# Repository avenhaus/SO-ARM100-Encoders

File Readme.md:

# <center>Magnetic Encoder Dummy Servo</center>

## Summary
This project is related to 
https://github.com/huggingface/lerobot
and
https://github.com/TheRobotStudio/SO-ARM100

It explores to use much cheaper magnetic encoders for the Leader Arm instead of the regular servos. These dummy servos are also much easier to move manually, as there is no gear train that needs to back drive the servo motor. This makes them ideal for the Leader Arm.

## Custom PCB

The custom PCB makes it possible to daisy chain magnetic encoders for much easier wiring. The PCB uses a microcontroller that emulates a FeeTech servo. The dummy servos can be connected to the same servo controller board and no special software is needed.

### Manufacturing
TODO: JLCPCB

### Cables and Connectors

FeeTech servos use 3-pin 5264 connectors. However, JST XH connectors are more common and pre-made cables are much easier to find. The PCB can be populated with either of the connector types. If JST connectors are used, an adapter needs to be made to connect to the 5264 connector on the controller board. Alternatively one can simply cut off one end from a pre-made cable and solder it directly to the controller board.

The dummy servos use very little current. So any gauge wire should be ok. However, if they are to be mixed with real servos on the same bus, wire gauge needs to be taken into consideration.

The servos use "reverse double head" cables (pin 1 connected to pin 1, etc.) although in a pinch it's also possible to switch the terminals on "same side' cables yourself.

JST XH: https://www.aliexpress.us/w/wholesale-JST-XH-3.html
JST XH cables: https://www.aliexpress.us/w/wholesale-xh-double-head.html

5264: https://www.aliexpress.us/w/wholesale-5264.html
5264 cables: https://www.aliexpress.us/w/wholesale-5264-double-head.html https://www.aliexpress.us/item/3256806128255434.html

### Magnets

Normally magnetic encoders use special, radially magnetized magnets.

Magnets https://www.aliexpress.us/w/wholesale-encoder-magnets.htm

However, it is also possible to use the regular, axially magnetized 6x3 disk magnets which are cheaper. They just have to be oriented sideways. Print the corresponding servo horn instead. N35 magnets are fine. Nothing fancy is needed.

https://www.amazon.com/s?k=6x3mm+magnet
https://www.aliexpress.us/w/wholesale-6x3-magnet.html

### Firmware Programming

See: [Firmware](Firmware)

### 3D Printed Servo Housing

## Off the Shelve Hardware

Instead of using a custom PCB it is also possible to use off the shelve parts. This requires more hand wiring.

### Magnetic Rotary Encoders
Currently there are two cheap and popular magnetic encoders on AliExpress, the AS5600 and the MT6701.
The AS5600 is older, has 12 bit resolution (4096) and supports only I2C. Since the chip has only one hard coded ID, that makes it hard to use when multiple of them are needed.
The MT6701 has 14 bit resolution (16,383) and also supports a SSI interface, which is similar to SPI.

AliExpress offers several MT6701 breakout boards some of which can be purchased in low quantities for less than $2 including magnet.

[AliExp MT6701](https://www.aliexpress.com/w/wholesale-MT6701.html)

<p>

The larger version only has the I2C pins on the header and must be modified to work with SSI. The trace to the middle pin of the header needs to be cut and IC pin 8 lifted and connected to that header pin instead. It is also slightly too large, sticking out a bit in front of the servo. It can be made to work, but the smaller board is much easier to use and therefor recommended. However the smaller board does not come with magnets. They must be purchased separately. Only radially magnetized magnets can be used. Normally disk magnets are magnetized axially. 

[AliExp Radial Magnets](https://www.aliexpress.us/item/3256804628068823.html)

### 3D Printed Servo Housing

There are two slightly different versions of the housing. The simple version does not retain the servo horns by itself. It relies on the structure of the robot arm to keep them in place. This version is slightly simpler and is used for the lower 4 arm servos.

The wrist and gripper need the horn to be held in place by the servo itself. For these joints the top is split into two parts and the horn axle is not just a straight cylinder.

**Big Board Alternative**

The [Dummy Servo](./Hardware) is 3D printed.

## Software

A simple [Arduino](./Arduino) / PlatformIO project is used to read the six encoders and send their values over a serial USB port to the PC.

On the PC side a small [Python](./Python) program receives the values from the serial port and uses the Feetech-SDK to control the servos of the follower arm.

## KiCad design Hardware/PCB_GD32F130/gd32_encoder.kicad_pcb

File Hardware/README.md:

# <center>3D Models</center>

## Custom PCB

The PCB can be populated with either an AS5600 or an MT6701 encoder. The MCU can automatically figure out which one is connected. However at the moment there are only non blocking drivers for the AS5600.

There are two versions of the PCB. One for the GD32F130 microcontroller, which is also used by Feetech servos. The other one uses a CH32V003 instead, which is cheaper. However no firmware has been written yet for the CH32V003 and the PCB has not been tested.

### Programming Dongles

The GD32F130 is programmed with a ST-LINK V2 dongle: https://www.aliexpress.us/item/3256805941217455.html / https://www.aliexpress.us/item/3256805308308820.html

The CH32V003  is programmed with a WCH-linkE dongle: https://www.aliexpress.us/item/3256804084637506.html

### Solder Stencil

[Cutting solder paste stencils from Mylar YouTube video](https://www.youtube.com/watch?v=mw0mskVCvis)
[make_stencil.py GitHub](https://github.com/bminch/Eclectronics)

- Open KicCAD PCB => Plot 
- Select layers: F. Paste and Edge Cuts
- Plot Format: SVG
- python make_stencil.py gd32_encoder

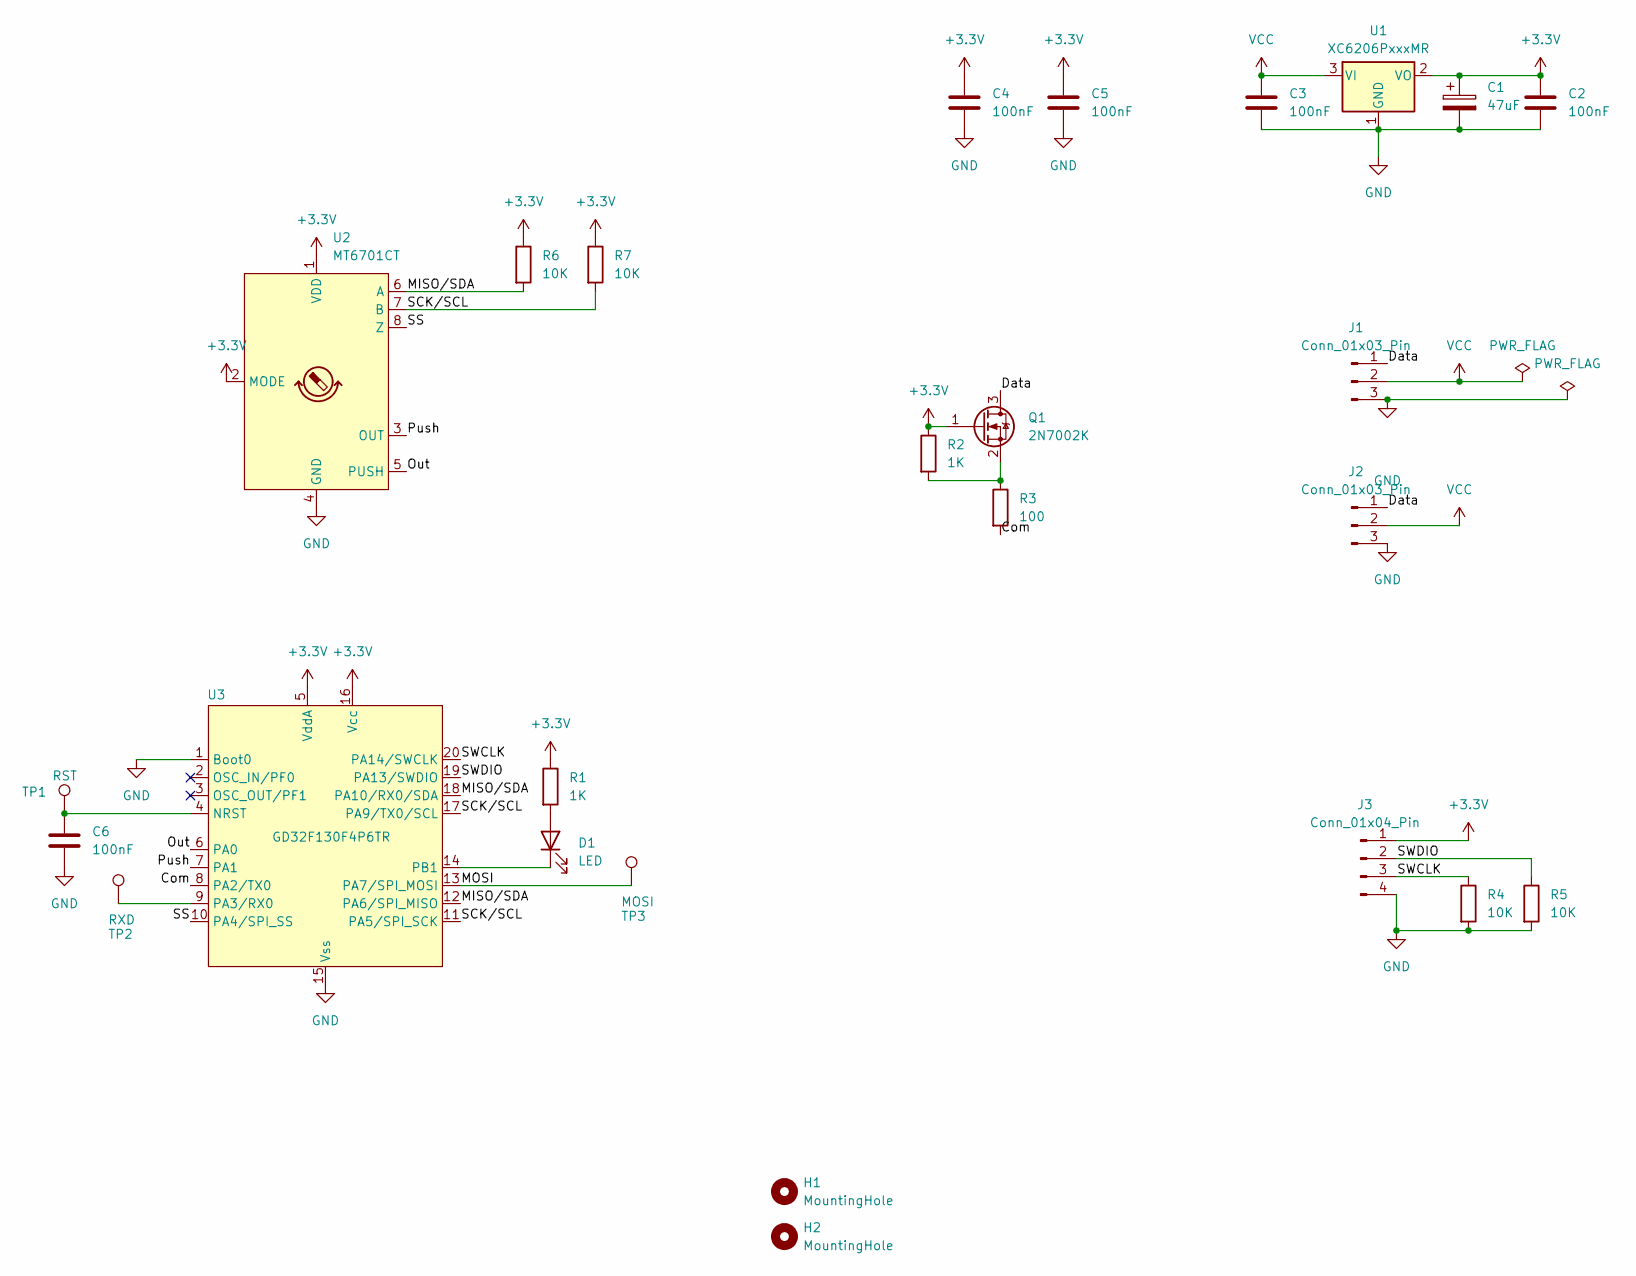
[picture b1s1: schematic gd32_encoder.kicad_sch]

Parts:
C1: 47uF; CP_EIA-3216-18_Kemet-A_Pad1.58x1.35mm_HandSolder
C2, C3, C4, C5, C6: 100nF; C_0603_1608Metric_Pad1.08x0.95mm_HandSolder
D1: LED; LED_0603_1608Metric_Pad1.05x0.95mm_HandSolder
H1, H2: MountingHole; MountingHole_2.2mm_M2_DIN965
J1, J2: Conn_01x03_Pin; JST_1x03_P2.50mm_Vertical
J3: Conn_01x04_Pin; PinHeader_1x04_P2.54mm_Vertical
Q1: 2N7002K; SOT-23
R1, R2: 1K; R_0603_1608Metric_Pad0.98x0.95mm_HandSolder
R3: 100; R_0603_1608Metric_Pad0.98x0.95mm_HandSolder
R4, R5, R6, R7: 10K; R_0603_1608Metric_Pad0.98x0.95mm_HandSolder
TP1: RST; PinHeader_1x01_P2.54mm_Vertical
TP2: RXD; TestPoint_Pad_D1.0mm
TP3: MOSI; TestPoint_Pad_D1.0mm
U1: XC6206PxxxMR; SOT-23-3
U2: MT6701CT; SO-8_3.9x4.9mm_P1.27mm
U3: GD32F130F4P6TR; TSSOP-20_4.4x6.5mm_P0.65mm

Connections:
+3.3V: C1.1, C2.1, C4.1, C5.1, J3.1, Q1.1 (G), R1.1, R2.1, R6.1, R7.1, U1.2 (VO), U2.1 (VDD), U2.2 (MODE), U3.5 (VddA), U3.16 (Vcc)
/Com: R3.2, U3.8 (PA2/TX0)
/Data: J1.1, J2.1, Q1.3 (D)
/MISO/SDA: R6.2, U2.6 (A), U3.12 (PA6/SPI_MISO), U3.18 (PA10/RX0/SDA)
/MOSI: TP3.1, U3.13 (PA7/SPI_MOSI); also elsewhere on the board
/Out: U2.5 (PUSH), U3.6 (PA0)
/Push: U2.3 (OUT), U3.7 (PA1)
/SCK/SCL: R7.2, U2.7 (B), U3.11 (PA5/SPI_SCK), U3.17 (PA9/TX0/SCL)
/SS: U2.8 (Z), U3.10 (PA4/SPI_SS)
/SWCLK: J3.3, R4.1, U3.20 (PA14/SWCLK)
/SWDIO: J3.2, R5.1, U3.19 (PA13/SWDIO)
GND: C1.2, C2.2, C3.2, C4.2, C5.2, C6.2, J1.3, J2.3, J3.4, R4.2, R5.2, U1.1 (GND), U2.4 (GND), U3.1 (Boot0), U3.15 (Vss)
unnamed: D1.2 (A), R1.2
unnamed: D1.1 (K), U3.14 (PB1)
unnamed: Q1.2 (S), R2.2, R3.1
unnamed: C6.1, TP1.1, U3.4 (NRST)
unnamed 16: TP2.1, U3.9 (PA3/RX0); also elsewhere on the board
VCC: C3.1, J1.2, J2.2, U1.3 (VI)

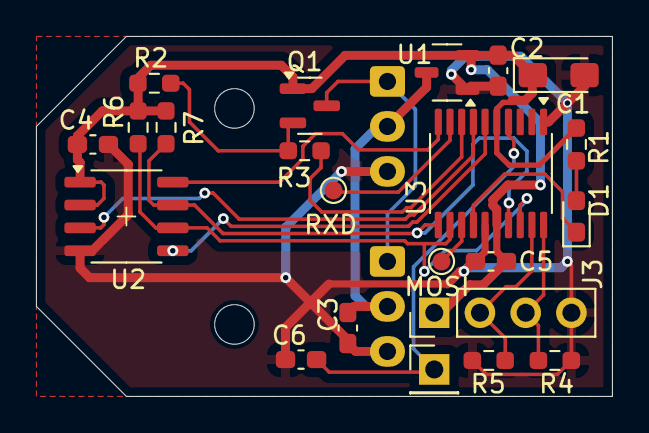
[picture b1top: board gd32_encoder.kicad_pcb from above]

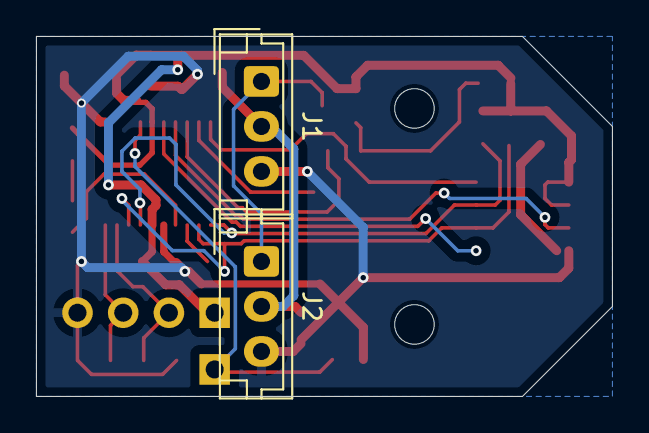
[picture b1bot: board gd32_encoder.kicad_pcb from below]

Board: 2 copper layers, 32.0 x 20.0 mm, 26 parts (2 on the bottom side), 18 nets.

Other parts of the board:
MOSI: MOSI; TestPoint_Pad_D1.0mm
RXD: RXD; TestPoint_Pad_D1.0mm

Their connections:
/MOSI: MOSI.1; also elsewhere on the board
unnamed 16: RXD.1; also elsewhere on the board

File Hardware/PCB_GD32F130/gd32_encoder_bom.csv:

Id,Designator,Footprint,Quantity,Designation,Supplier and ref
1,"R4,R5,R7,R6",R_0603_1608Metric_Pad0.98x0.95mm_HandSolder,4,10K,
4,C1,CP_EIA-3216-18_Kemet-A_Pad1.58x1.35mm_HandSolder,1,47uF,
5,"C2,C5,C3,C6,C4",C_0603_1608Metric_Pad1.08x0.95mm_HandSolder,5,100nF,
6,"R1,R2",R_0603_1608Metric_Pad0.98x0.95mm_HandSolder,2,1K,
7,U3,TSSOP-20_4.4x6.5mm_P0.65mm,1,GD32F130F4P6TR,
8,U2,SO-8_3.9x4.9mm_P1.27mm,1,MT6701CT,
9,R3,R_0603_1608Metric_Pad0.98x0.95mm_HandSolder,1,100,
11,D1,LED_0603_1608Metric_Pad1.05x0.95mm_HandSolder,1,LED,
12,U1,SOT-23-3,1,XC6206PxxxMR,
14,Q1,SOT-23,1,2N7002K,

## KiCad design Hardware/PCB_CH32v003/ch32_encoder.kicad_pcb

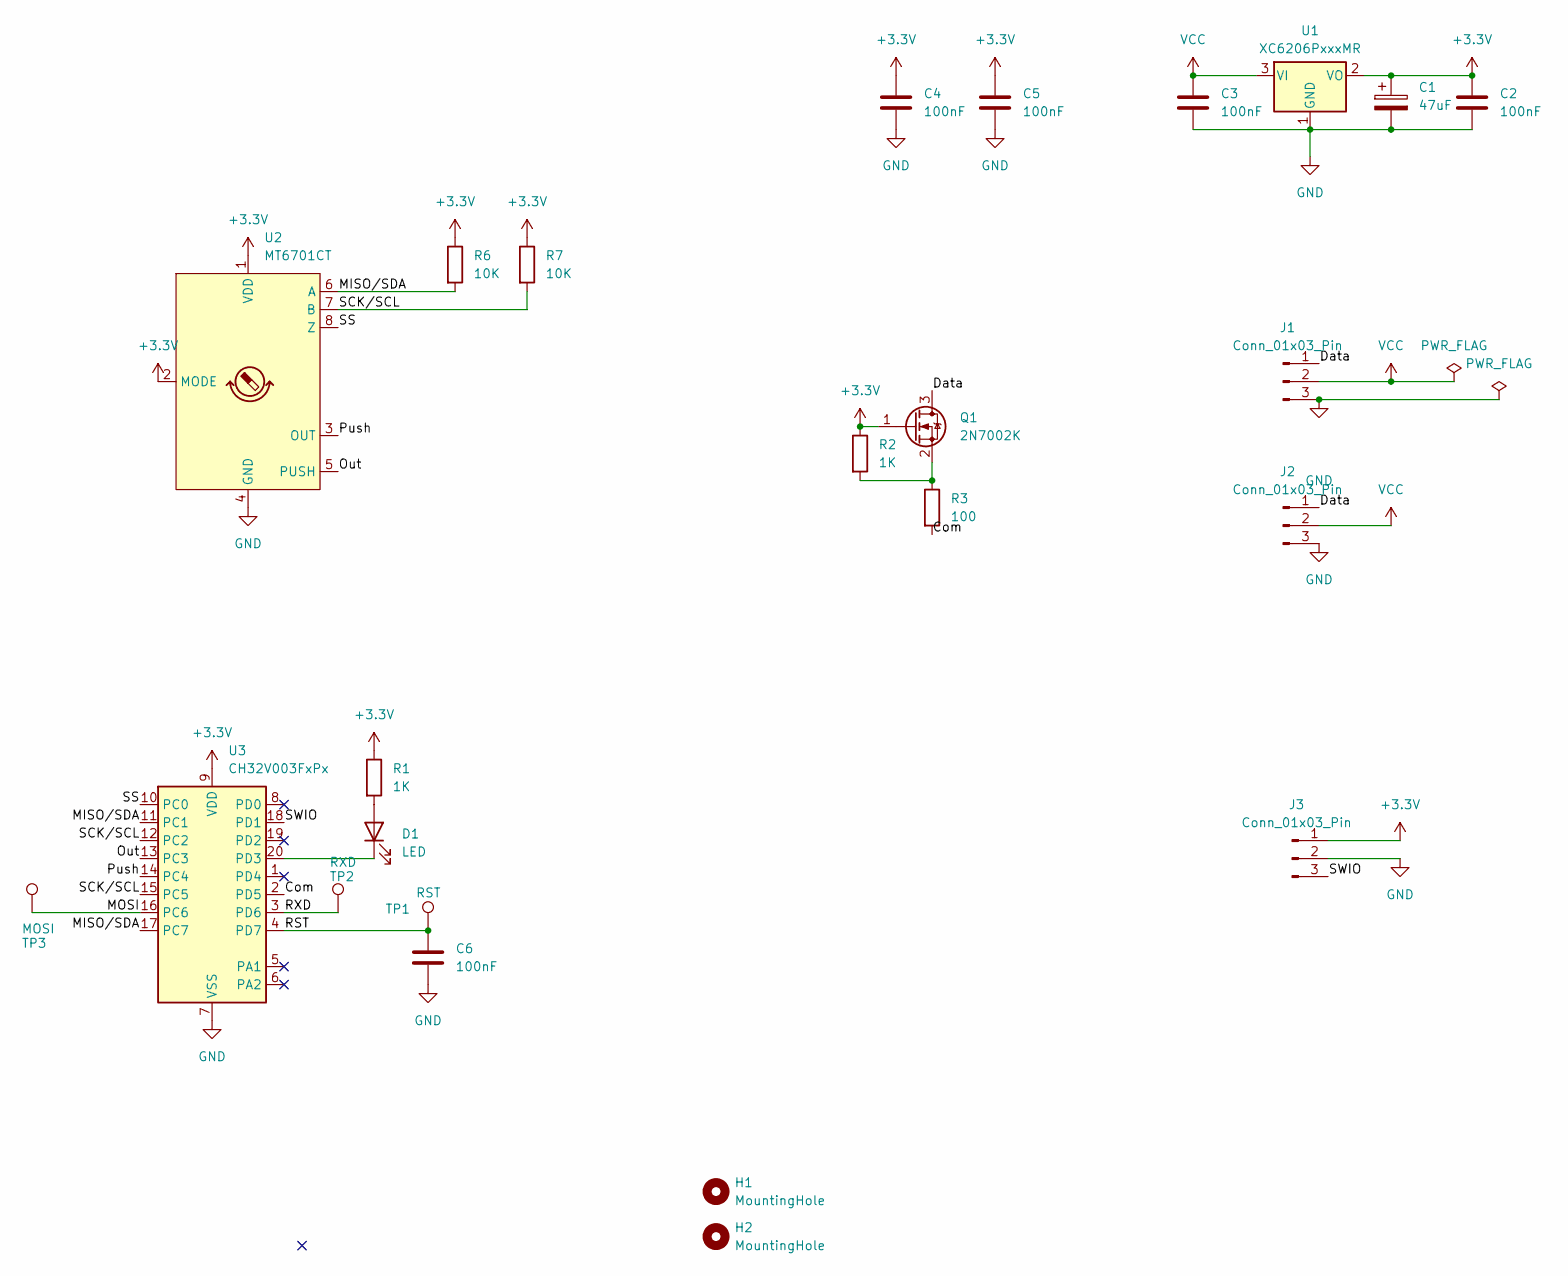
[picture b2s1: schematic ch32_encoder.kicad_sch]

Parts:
C1: 47uF; CP_EIA-3216-18_Kemet-A_Pad1.58x1.35mm_HandSolder
C2, C3, C4, C5, C6: 100nF; C_0603_1608Metric_Pad1.08x0.95mm_HandSolder
D1: LED; LED_0603_1608Metric_Pad1.05x0.95mm_HandSolder
H1, H2: MountingHole; MountingHole_2.2mm_M2_DIN965
J1, J2: Conn_01x03_Pin; JST_1x03_P2.50mm_Vertical
J3: Conn_01x03_Pin; PinHeader_1x03_P2.54mm_Vertical
Q1: 2N7002K; SOT-23
R1, R2: 1K; R_0603_1608Metric_Pad0.98x0.95mm_HandSolder
R3: 100; R_0603_1608Metric_Pad0.98x0.95mm_HandSolder
R6, R7: 10K; R_0603_1608Metric_Pad0.98x0.95mm_HandSolder
TP1: RST; PinHeader_1x01_P2.54mm_Vertical
TP2: RXD; TestPoint_Pad_D1.0mm
TP3: MOSI; TestPoint_Pad_D1.0mm
U1: XC6206PxxxMR; SOT-23-3
U2: MT6701CT; SO-8_3.9x4.9mm_P1.27mm
U3: CH32V003FxPx; TSSOP-20_4.4x6.5mm_P0.65mm

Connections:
+3.3V: C1.1, C2.1, C4.1, C5.1, J3.1, Q1.1 (G), R1.1, R2.1, R6.1, R7.1, U1.2 (VO), U2.1 (VDD), U2.2 (MODE), U3.9 (VDD)
/Com: R3.2, U3.2 (PD5)
/Data: J1.1, J2.1, Q1.3 (D)
/MISO/SDA: R6.2, U2.6 (A), U3.11 (PC1), U3.17 (PC7)
/MOSI: TP3.1, U3.16 (PC6); also elsewhere on the board
/Out: U2.5 (PUSH), U3.13 (PC3)
/Push: U2.3 (OUT), U3.14 (PC4)
/RST: C6.1, TP1.1, U3.4 (PD7)
/RXD: TP2.1, U3.3 (PD6); also elsewhere on the board
/SCK/SCL: R7.2, U2.7 (B), U3.12 (PC2), U3.15 (PC5)
/SS: U2.8 (Z), U3.10 (PC0)
/SWIO: J3.3, U3.18 (PD1)
GND: C1.2, C2.2, C3.2, C4.2, C5.2, C6.2, J1.3, J2.3, J3.2, U1.1 (GND), U2.4 (GND), U3.7 (VSS)
unnamed: D1.2 (A), R1.2
unnamed: D1.1 (K), U3.20 (PD3)
unnamed: Q1.2 (S), R2.2, R3.1
VCC: C3.1, J1.2, J2.2, U1.3 (VI)

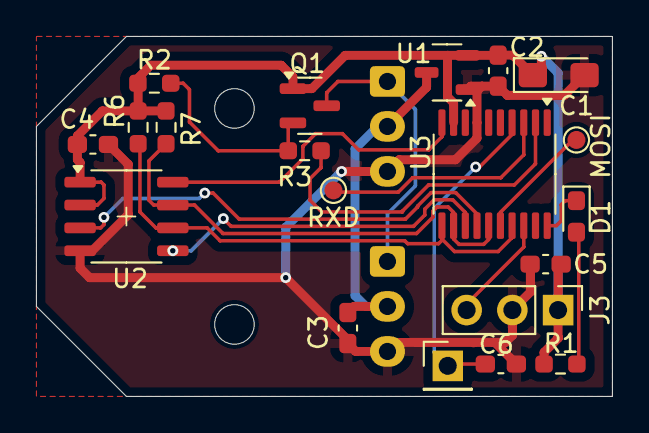
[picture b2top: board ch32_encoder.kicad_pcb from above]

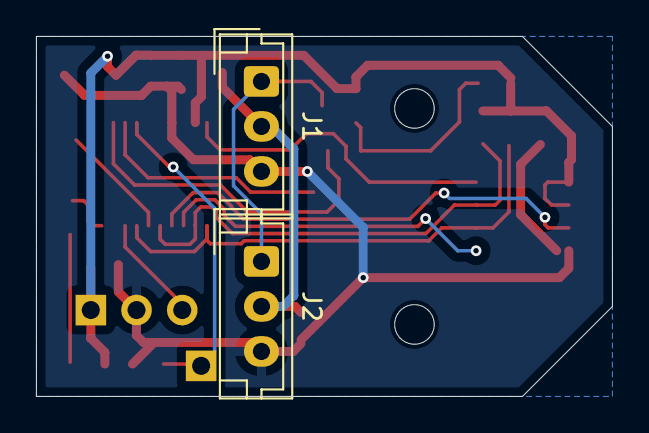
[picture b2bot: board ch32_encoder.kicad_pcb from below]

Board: 2 copper layers, 32.0 x 20.0 mm, 24 parts (2 on the bottom side), 17 nets.

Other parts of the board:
MOSI: MOSI; TestPoint_Pad_D1.0mm
RXD: RXD; TestPoint_Pad_D1.0mm

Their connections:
/MOSI: MOSI.1; also elsewhere on the board
/RXD: RXD.1; also elsewhere on the board

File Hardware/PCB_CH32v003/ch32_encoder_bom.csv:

"Id";"Designator";"Footprint";"Quantity";"Designation";"Supplier and ref";
1;"MOSI";"TestPoint_Pad_D1.0mm";1;"MOSI";;;
2;"TP1";"PinHeader_1x01_P2.54mm_Vertical";1;"RST";;;
3;"C1";"CP_EIA-3216-18_Kemet-A_Pad1.58x1.35mm_HandSolder";1;"47uF";;;
4;"C2,C5,C3,C6,C4";"C_0603_1608Metric_Pad1.08x0.95mm_HandSolder";5;"100nF";;;
5;"R1,R2";"R_0603_1608Metric_Pad0.98x0.95mm_HandSolder";2;"1K";;;
6;"J3";"PinHeader_1x03_P2.54mm_Vertical";1;"Conn_01x03_Pin";;;
7;"U2";"SO-8_3.9x4.9mm_P1.27mm";1;"MT6701CT";;;
8;"R3";"R_0603_1608Metric_Pad0.98x0.95mm_HandSolder";1;"100";;;
9;"R7,R6";"R_0603_1608Metric_Pad0.98x0.95mm_HandSolder";2;"10K";;;
10;"D1";"LED_0603_1608Metric_Pad1.05x0.95mm_HandSolder";1;"LED";;;
11;"U1";"SOT-23-3";1;"XC6206PxxxMR";;;
12;"RXD";"TestPoint_Pad_D1.0mm";1;"RXD";;;
13;"Q1";"SOT-23";1;"2N7002K";;;
14;"U3";"TSSOP-20_4.4x6.5mm_P0.65mm";1;"CH32V003FxPx";;;
15;"J1,J2";"JST_1x03_P2.50mm_Vertical";2;"Conn_01x03_Pin";;;

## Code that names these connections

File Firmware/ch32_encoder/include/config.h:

#pragma once

#define SWIO_PIN PD1 // Program / Debug

#define LED_PIN PD3
#define TXD_PIN PD5
#define RXD_PIN PD6

#define SDA_PIN PC1
#define SCL_PIN PC2

#define OUT_PIN PC3
#define PUSH_PIN PC4

#define SS_PIN PC0
#define SCK_PIN PC5
#define MOSI_PIN PC6
#define MISO_PIN PC7

#define DEBUG 1

//#define millis() (SysTick->CNT / DELAY_MS_TIME)

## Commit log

2024-09-24 small enhancment and work on documentation
2024-10-04 documentation
2024-10-04 added 3D models
2024-10-04 more documentation
2024-10-05 big board
2024-10-13 track test added
2024-10-16 added custom PCB
2024-11-06 Added PCB for CH32V003, which is a bit cheaper. New revision of GD32F130 PCB.
2024-11-13 Start of GD32130 Encoder firmware
2024-11-17 Implemented non blocking GD32F130 drivers for I2C and AS5600
2024-11-21 Added solder stencil, images, PCB 3d model and schematic PDF.
2024-11-27 Work on documentation
2024-12-03 Updated 3.3V regulator with HT7533S that supports 12V input. / Mentioned AS5600 compatibility.
2024-12-03 Disabled EEPROM for GD32F130F4. The EEPROM driver uses too much RAM for this device. Servo ID needs to be hard coded for now.
2024-12-04 Changed PCB height for more connector clearance. Added Fusion 360 file.
2024-12-11 Reorganized 3D modles
2024-12-13 Fixes for V1 3D model
2024-12-14 Added feature: Torque Switch = 128 => Set Center Position
2024-12-15 Work on Bulk Read command
2024-12-15 Start of CH32V003 firmware
2024-12-15 Work on Sync Read
2024-12-16 Some code cleanup
2024-12-17 sync read bug fix
2025-01-04 Fixed R2 resistor value
